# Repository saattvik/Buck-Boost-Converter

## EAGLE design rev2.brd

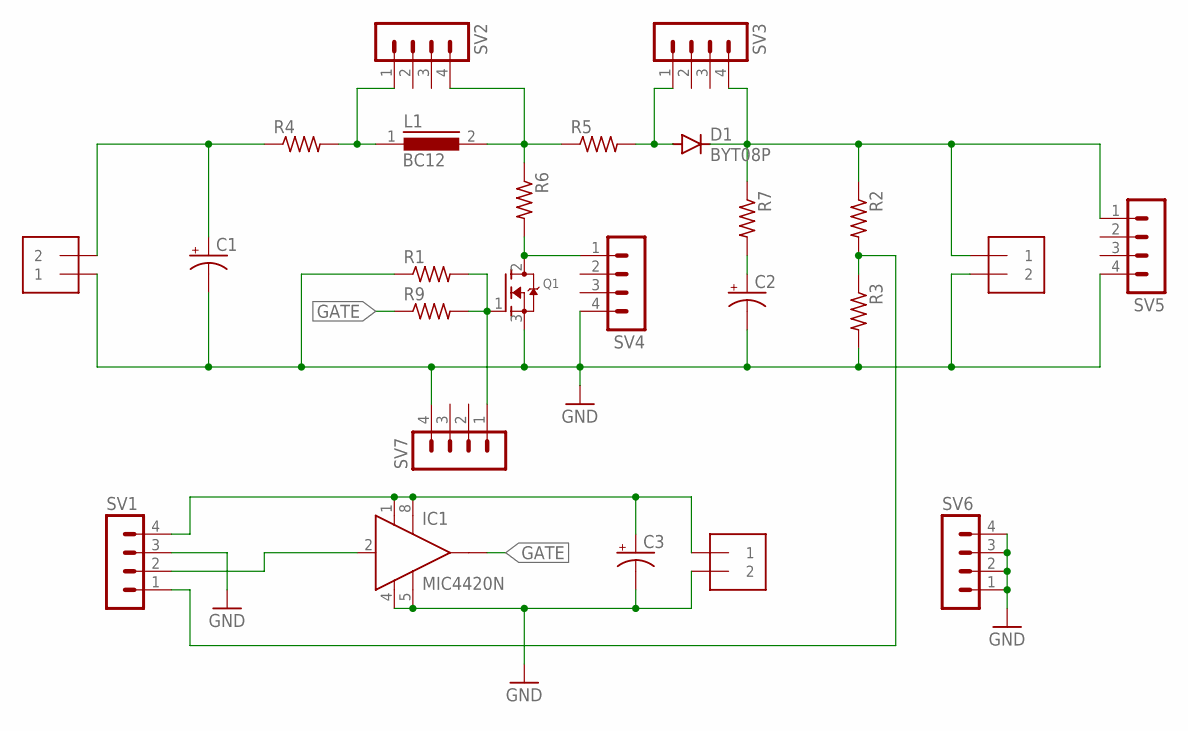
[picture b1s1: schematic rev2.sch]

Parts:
C1, C2: CPOL-USE7.5-18; E7,5-18
C3: CPOL-USE2.5-6; E2,5-6
D1: BYT08P; TO220ACS
IC1: MIC4420N; DIL08
J1, J2, J3: 1X2-3.5MM
L1: BC12
Q1: MOSFET-NGDS_TO220V; TO220V
R1, R2, R3: R-US_0207/7; 0207/7
R4, R5, R6, R7: R-US_0613/15; P0613/15
R9: R-US_0309/12; 0309/12
SV1, SV2, SV3, SV4, SV5, SV6, SV7: MA04-1

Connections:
GATE: IC1.6 (OUT), R9.1
GND: C1.-, C2.-, C3.-, IC1.4 (GND), IC1.5 (GND1), J1.1, J2.2, J3.2, Q1.3 (S), R1.1, R3.2, SV1.3, SV4.4, SV5.4, SV6.1, SV6.2, SV6.3, SV6.4, SV7.4
unnamed: C1.+, J1.2, R4.1
unnamed: L1.1, R4.2, SV2.1
unnamed: L1.2, R5.1, R6.1, SV2.4
unnamed: D1.A, R5.2, SV3.1
unnamed: C3.+, IC1.1 (VS), IC1.8 (VS1), J3.1, SV1.4
unnamed: Q1.2 (D), R6.2, SV4.1
unnamed: Q1.1 (G), R1.2, R9.2, SV7.1
unnamed: C2.+, R7.2
unnamed: D1.C, J2.1, R2.1, R7.1, SV3.4, SV5.1
unnamed: R2.2, R3.1, SV1.1
unnamed: IC1.2 (IN), SV1.2

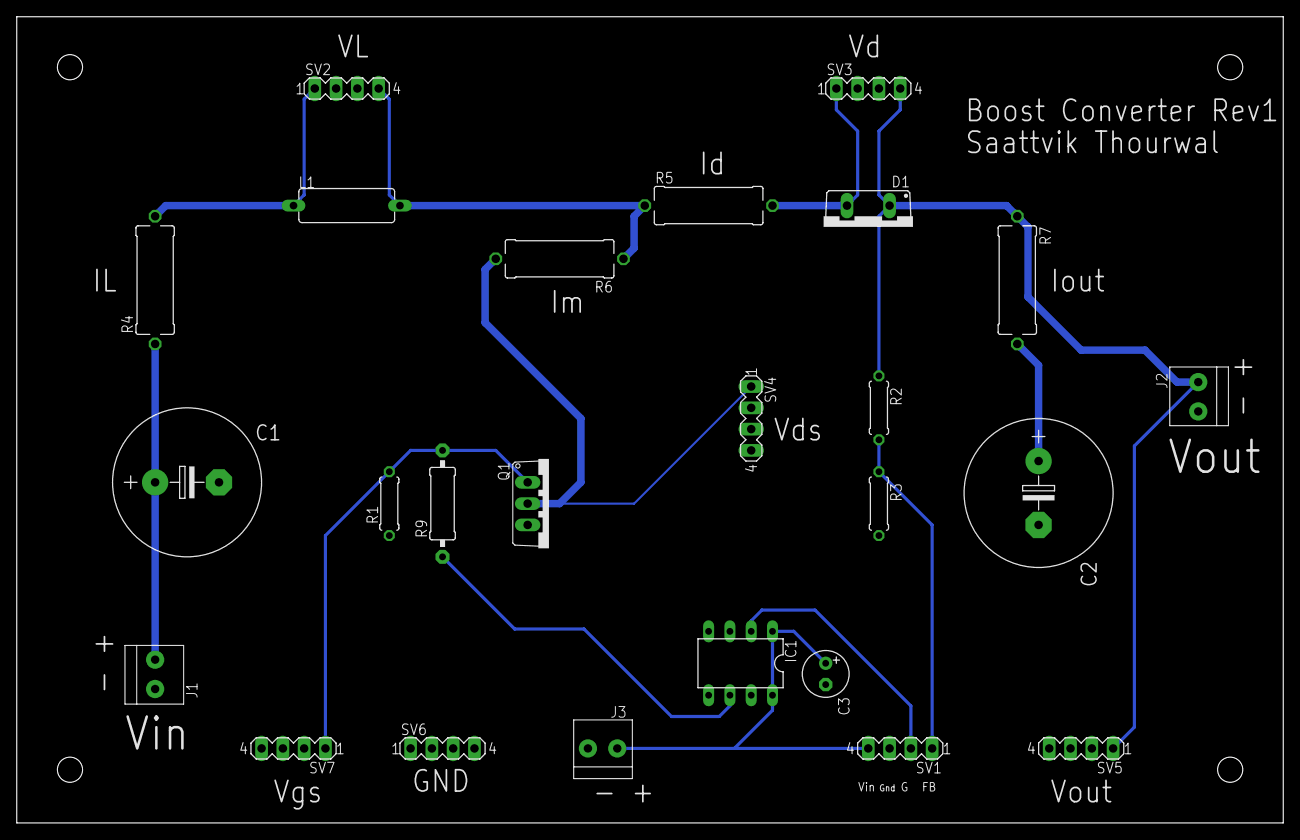
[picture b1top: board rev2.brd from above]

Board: 2 copper layers, 151.1 x 96.2 mm, 25 parts (0 on the bottom side), 13 nets.
